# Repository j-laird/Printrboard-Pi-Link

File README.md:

# Printrboard-Pi-Link
 The Printrboard-Pi-Link is a Printed Circuit Board Assembly that connects a Printrbot Printrboard with a newer-model Raspberry Pi (B+, Raspberry Pi 2 B, etc).

## Feature Overview
The Printrboard-Pi-Link has the following unique features:
* Accepts 12v input on either 4-pin(ATX 12V) or 6-pin(PCI-E) Molex Minifit-Jr connectors
* Supplies switched (see below) 12V power to Printrboard via screw-type Phoenix connector
* Produces high-current (3A max) 5V power for Raspberry Pi (no wall-wart needed)
* Uses UART connection on Raspberry Pi GPIO (replaces micro-USB connection to Printrboard)
* Exposes 3 GPIO intended for:
  * Printrbot "ready to print" LED
  * Printrbot "push to print" button
  * Wi-Fi mode switch between AP and infrastructure mode
* Allows the Raspberry Pi to shutoff 12V power to Printrboard (in case bad things happen)
* Exposes an external safety 12v shutoff for user-supplied circuits (smoke detector, etc.)
* Adds automotive-style ATO fuse in 12V path

### BUILD INFORMATION

If you would like to make your own Printrboard-Pi-Link and provide some beta feedback, please be aware that the Printrboard-Pi-Link board uses some tiny surface mount components and is an advanced soldering project that will also require flashing the firmware on your Printrboard.

To order your own PCB's this git repository can be downloaded as a zip and uploaded directly to [OSHPark](https://www.oshpark.com/) where you can order three boards for less than $30.

All parts but L1 (inductor) can be sourced from Digikey. A pre populated [shopping cart](http://www.digikey.com/short/71w84q) with enough parts to build this (minus ribbon cable and 16awg wire) is available.   NOTE THIS CART IS FOR REV B.  Rev A used a different fuse holder.

[Bill of Materials](https://docs.google.com/spreadsheets/d/1JWQViEhnYA_FKTI_PxGergLy6LZkPQN6mZyLyM8gfQU/edit?usp=sharing)

### CONFIGURATION

When creating the Printrboard-Pi-Link, I recognized that some printrbot models "hide" the Printrboard underneath the printer, while others leave the board exposed.  When this board is installed on the Raspberry Pi, only two cables need be connected from this board to the Printrboard: a ribbon cable to EXP1, and a 4/6-wire power cable to the power connection.  

It is expected that a short ribbon cable can be supplied for users who want the Raspberry Pi located back-to-back with the Printrboard, and a longer ribbon cable can be supplied for those "hidden" Printrboards.  Similarly, the supplied 4 or 6-pin power extension has only a connector on one end -- and can be cut to length by the customer (thus the screw terminals).

### FIRMWARE

In order to enable the hardware UART on the Printrboard (rather than the USB CDC serial port), use of this board requires a special build of firmware.  Standard firmware versions will not communicate directly, although it would be possible to communicate using the traditional micro USB cable to one of the Raspberry Pi's USB ports.

There are instructions available for flashing the Printrboard firmware available from [Printrbot support](http://help.printrbot.com/Guide/How+to+Reflash+Firmware).

* [Rev D Firmware](https://github.com/j-laird/Marlin/releases/tag/PiBachelor--V3)
* [Rev F4/F5 Firmware](https://github.com/j-laird/Marlin/releases/tag/PiLassen-V3)

### RASPBERRY PI / OCTOPRINT SETUP

The hardware UART on the Raspberry Pi must be enabled.  Run raspi-config and select Advanced Options.  Under Serial, disable login over serial port.

Modify /boot/config.txt to add init_uart_clock=4000000

You may need to add the UART serial port to octoprint under Settings > Serial Connection.  In the Additional serial ports section add /dev/ttyAMA0 so that you can select the UART port in OctoPrint.  250000 is the baudrate that has been verified to be working.

Install the wiringPi library using the following [instructions](https://projects.drogon.net/raspberry-pi/wiringpi/download-and-install/).

Modify ~/.octoprint/config.yaml to add the following lines under system: actions to add the commands to the OctoPrint System menu.

    - action: shutdown printbot
      command: gpio -g write 2 1
      name: Kill Printrboard 12V supply
    - action: poweron printrbot
      command: gpio -g write 2 0
      name: Enable Printrboard 12V supply

Modify /etc/init.d/octoprint to add the following lines in the do_start() function, right above RETVAL="$?"

    gpio -g export 2 out
    gpio -g mode 2 out
    gpio -g write 2 0

# DISCLAIMERS

Although using a Raspberry Pi with [Octoprint](http://octoprint.org/) is a fabulous way to run a print job semi-unattended, and this board enables additional features in that regard, it is **categorically not endorsed/recommended** as a safe practice.  The additional safety and remote shutdown features should not encourage you to leave the printer at home/work printing.  For those of you who void warranties, tear up manuals, and eat your steak rare -- hopefully this provides additional safety margin.

But seriously - don't print unattended.

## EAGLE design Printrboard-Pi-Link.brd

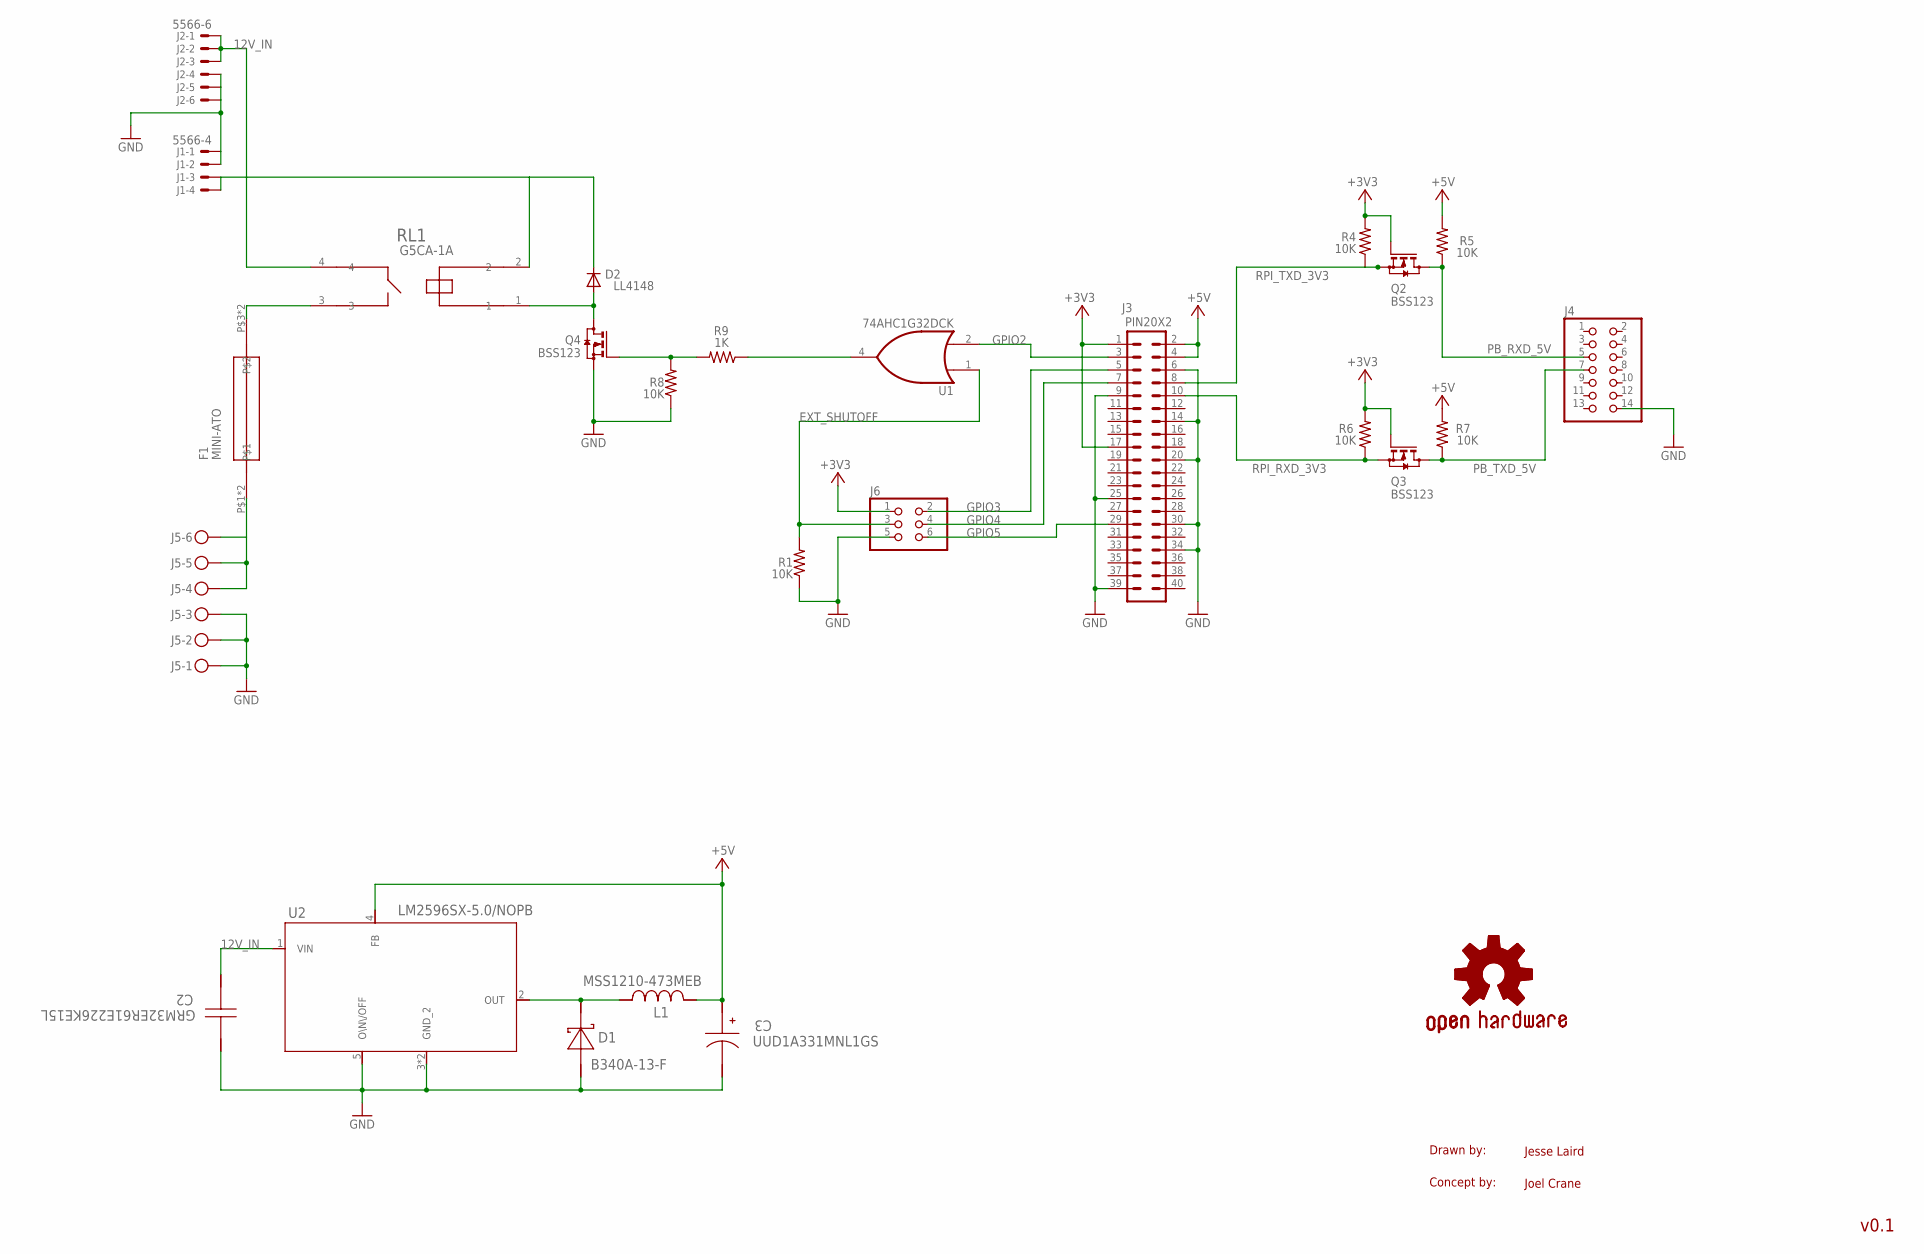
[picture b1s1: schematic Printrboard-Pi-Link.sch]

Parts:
C2: GRM32ER61E226KE15L; 1210
C3: UUD1A331MNL1GS; SM_RADIAL_8MM
D1: B340A-13-F; SMA
D2: LL4148; SOD80C
F1: MINI-ATO; BK-6011
GOLD_ORB_SM1: OSHWLOGO_GOLD_ORB_SM; OSHW2
J1: 5566-4
J2: 5566-6
J3: PIN20X2; PIN_20X2
J4: PINHD-2X7; 2X07
J5: MKDSN1,5/6-5,08
J6: PINHD-2X3; 2X03
L1: MSS1210-473MEB; MSS1210
Q2, Q3, Q4: BSS123; SOT23
R1, R4, R5, R6, R7, R8: 10K; R0603
R9: 1K; R0603
RL1: G5CA-1A; G5CA
U1: 74AHC1G32DCK; SC70-5
U2: LM2596SX-5.0/NOPB; TS5B

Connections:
12V_IN: C2.1, D2.C, J1.3, J1.4, J2.1, J2.2, J2.3, RL1.2, RL1.4, U2.1 (VIN)
+3V3: J3.1, J3.17, J6.1, Q2.1 (G), Q3.1 (G), R4.2, R6.2
+5V: C3.1 (+), J3.2, J3.4, L1.2, R5.2, R7.2, U2.4 (FB)
EXT_SHUTOFF: J6.3, R1.2, U1.1 (I0)
GND: C2.2, C3.2 (-), D1.2 (A), J1.1, J1.2, J2.4, J2.5, J2.6, J3.6, J3.9, J3.14, J3.20, J3.25, J3.30, J3.34, J3.39, J4.14, J5.1, J5.2, J5.3, J6.5, Q4.2 (S), R1.1, R8.1, U1.3 (GND), U2.3 (GND_2), U2.5 (O\N\/OFF), U2.6 (GND_2)
GPIO2: J3.3, U1.2 (I1)
GPIO3: J3.5, J6.2
GPIO4: J3.7, J6.4
GPIO5: J3.29, J6.6
unnamed: F1.P$3, F1.P$4, RL1.3
unnamed: R9.1, U1.4 (O)
unnamed: D1.1 (K), L1.1, U2.2 (OUT)
unnamed: D2.A, Q4.3 (D), RL1.1
unnamed: Q4.1 (G), R8.2, R9.2
unnamed: F1.P$1, F1.P$2, J5.4, J5.5, J5.6
PB_RXD_5V: J4.5, Q2.3 (D), R5.1
PB_TXD_5V: J4.7, Q3.3 (D), R7.1
RPI_RXD_3V3: J3.10, Q3.2 (S), R6.1
RPI_TXD_3V3: J3.8, Q2.2 (S), R4.1
VCC: U1.5 (VCC)

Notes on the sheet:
Drawn by:
Concept by:
Jesse Laird
v0.1
Joel Crane

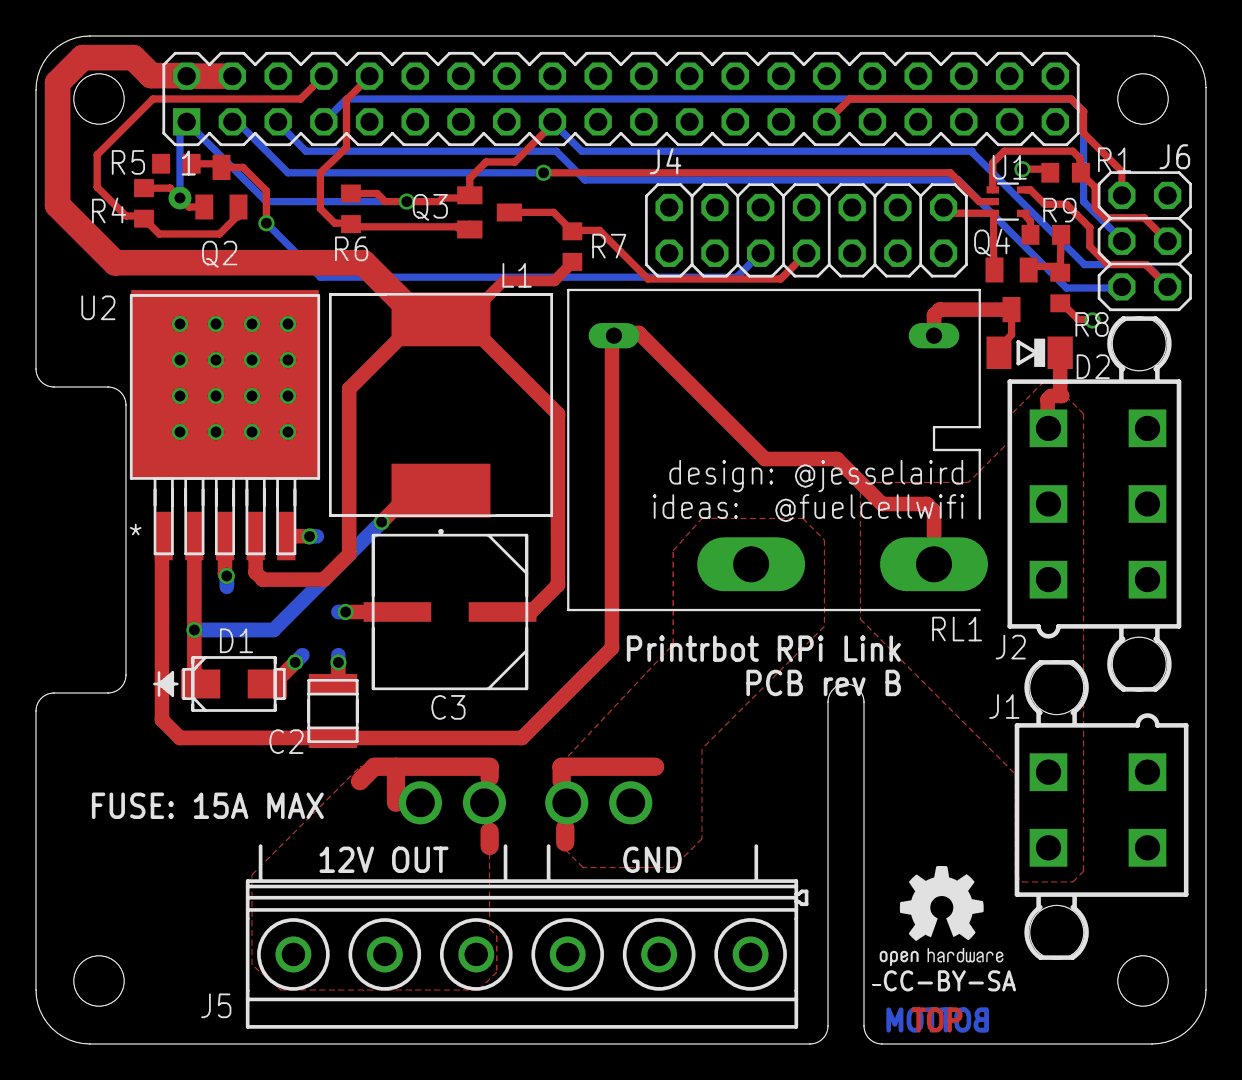
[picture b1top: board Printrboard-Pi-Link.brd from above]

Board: 2 copper layers, 65.0 x 56.0 mm, 26 parts (0 on the bottom side), 19 nets.

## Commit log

2015-05-22 First Fabrication - Rev A
    First fabrication @ OSHPARK
2015-06-18 Added Digikey BOM
    Added Digikey cart for components
2015-06-20 Rev_B
    Fixes missing 3v3 connection on NOR gate; reduces fuse size from ATO to
    mini-ATO/automotive fuse.
2015-06-26 Added firmware links and wiringPi setup
2015-06-27 Added Google Docs BOM
2015-06-27 Correct the spelling of enabled
2015-07-07 Update links and headings, add PCBA photo, make octoprint settings section code
2015-07-08 Add additional build information and OSHPark images
2015-07-10 Add UART Octoprint documentation and link to printrbot firmware flashing help page
2015-07-10 add octoprint settings images, other minor formatting adjustments

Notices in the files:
Printrboard-Pi-Link.brd:
CC-BY-SA
